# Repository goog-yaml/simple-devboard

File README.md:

# Mk1

Mk1 is the internal name of this project. I am using this as a way to learn about PCB design and embedded systems and make a "final" out of it. The "final" that I have made is a simple, low-cost, ESP32-S3 development board. I originally added tons of sensors and complexity but shaved them off to make the project more attainable. The board functions similar to most other boards, boasting a USB to Serial converter, a sample IMU sensor for SPI testing, and extra essentials like auto reset circuits and a voltage regulator. The board has gone well but I advise most to not use any of these designs for future projects of their own. If you do, don't be surprised when it blows up in your face.

Horizons reviews please check in the /REVIEWERS folder

Journal logs are in the /documentation folder of this repo

The schematic breakdown goes as follows:

# The ESP32-S3

The power rails start with two decoupling capacitors before then merging with reset and boot circuit through pull up resistors

# The IMU

The IMU is a simple MPU-9250 following the schematic posted its online datasheet

# USB to Serial IC

The USB to Serial IC is a FTDI FT231XQ also following the schematic posted in its datasheet

# Auto reset

The auto reset circuit is a set of two 2N3984 transistors that feed into the DTR and RTS pins of the FT231XQ, When a handshake is sent by the flashing device the devboard can enter bootloader states without the need of a button press on the board, though the buttons are still included as a fallback

# USB Port

The port is simple with only two 5K1 resistors for USB power negotiation on both sides.

# Voltage regulator

The voltage regulator includes one TLV75533PDRV from TI and decoupling capacitors on power ins and outs. And the reset pin is tied to power to keep the chip on while the board has power.

# Overall

The PCB is extremely messy.

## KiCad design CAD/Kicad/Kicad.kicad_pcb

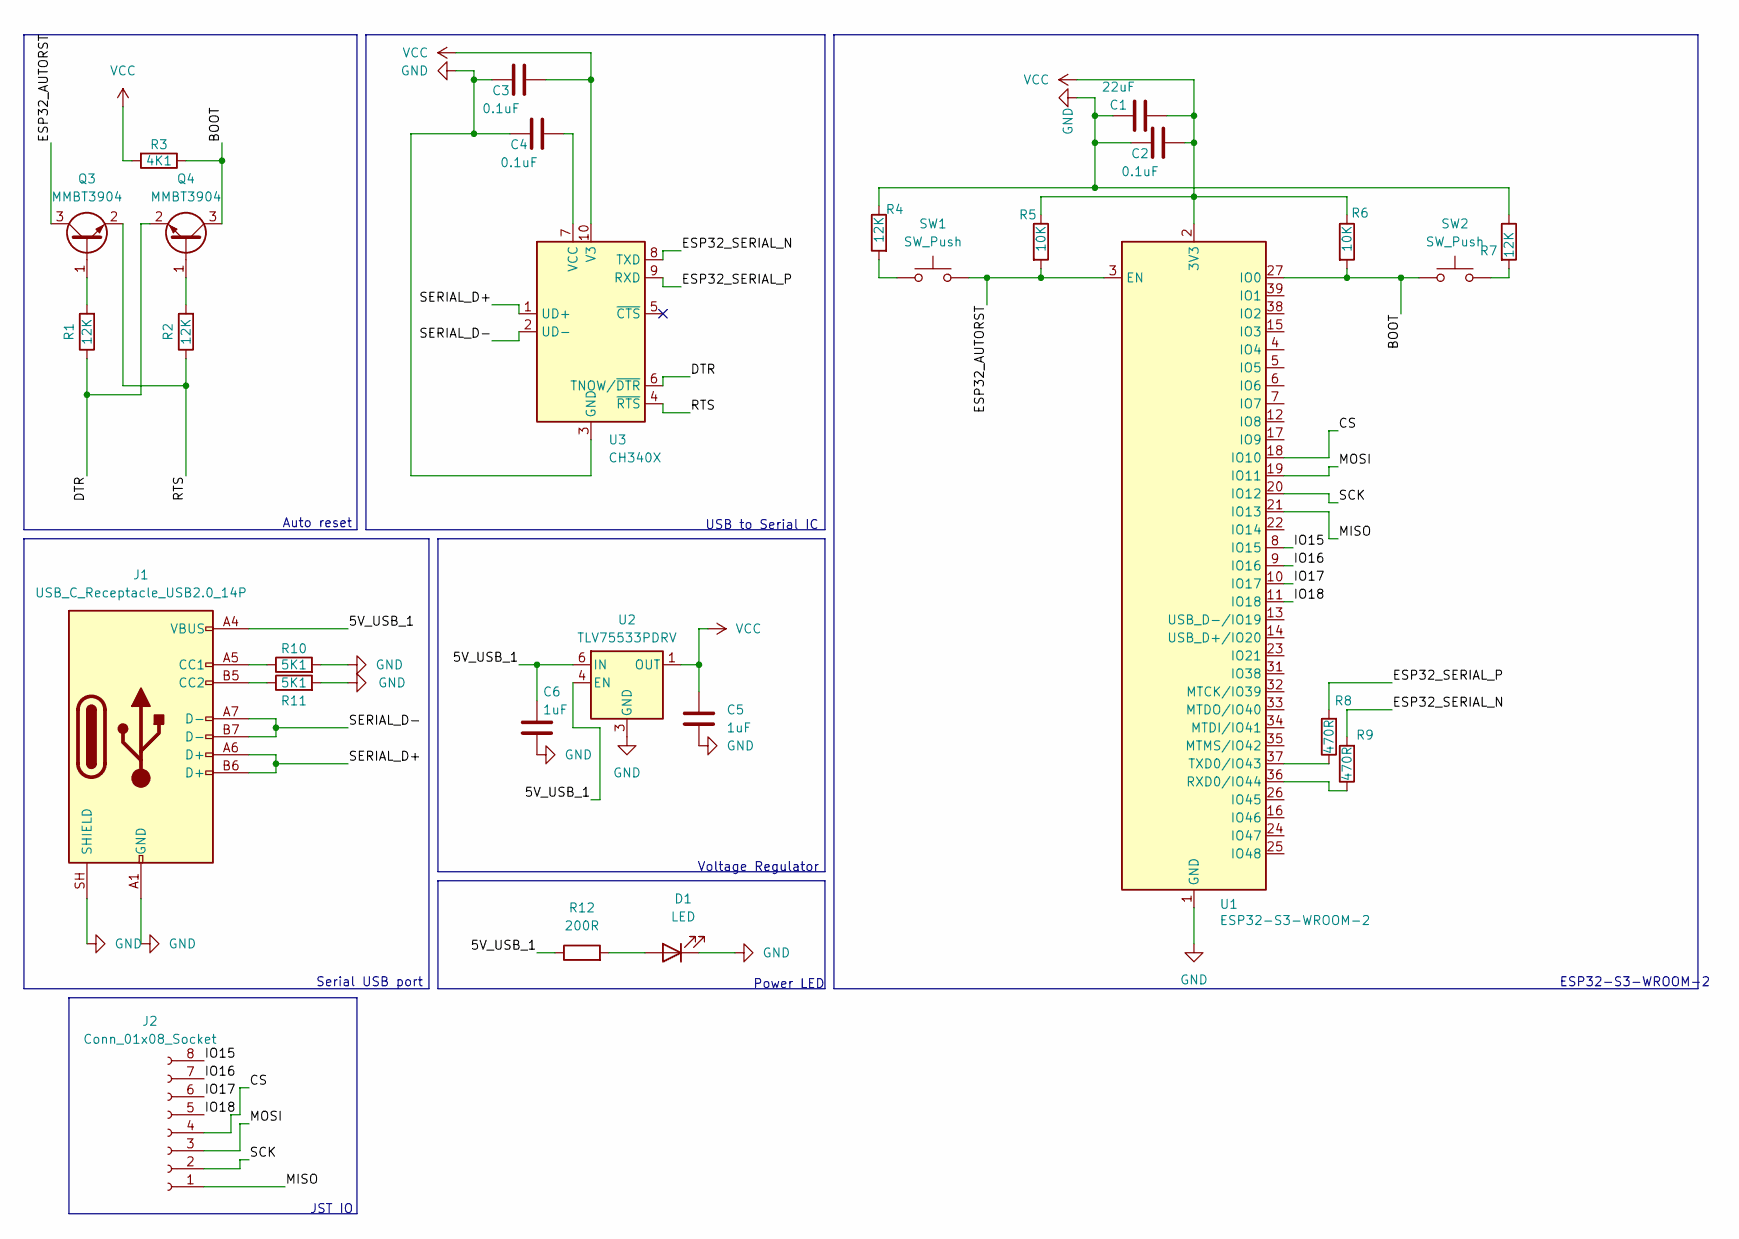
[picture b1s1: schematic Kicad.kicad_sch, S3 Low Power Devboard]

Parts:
C1: 22uF; C_01005_0402Metric; LCSC Part # C105226
C2, C3, C4: 0.1uF; C_01005_0402Metric; LCSC Part # C1525
C5, C6: 1uF; C_01005_0402Metric; LCSC Part # C52923
D1: LED; LED_0201_0603Metric; LCSC Part # C2286
J1: USB_C_Receptacle_USB2.0_14P; USB_C_Receptacle_G-Switch_GT-USB-7025; LCSC Part # C963213
J2: Conn_01x08_Socket; JST_EH_S8B-EH_1x08_P2.50mm_Horizontal; LCSC Part # C265106
Q3, Q4: MMBT3904; SOT-23
R1, R2, R4, R7: 12K; R_0201_0603Metric; LCSC Part # C25752
R3: 4K1; R_0201_0603Metric; LCSC Part # C4109
R5, R6: 10K; R_0201_0603Metric; LCSC Part # C131361
R8, R9: 470R; R_0201_0603Metric; LCSC Part # C177340
R10: 5K1; R_0201_0603Metric; LCSC Part # C25905
R11: 5K1; R_0201_0603Metric; LCSC Part # C177348
R12: 200R; R_01005_0402Metric; LCSC Part # C25087
SW1, SW2: SW_Push; SW_SPST_B3U-1000P; LCSC Part # C231329
U1: ESP32-S3-WROOM-2; LCSC Part # C42417293
U2: TLV75533PDRV; WSON-6-1EP_2x2mm_P0.65mm_EP1x1.6mm; LCSC Part # C2861750
U3: CH340X; MSOP-10_3x3mm_P0.5mm; LCSC Part # C3035748

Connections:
/5V_USB_1: C6.1, J1.A4 (VBUS), J1.A9 (VBUS), J1.B4 (VBUS), J1.B9 (VBUS), R12.1, U2.4 (EN), U2.6 (IN)
/BOOT: Q4.3 (C), R3.1, R6.2, SW2.1, U1.27 (IO0)
/CS: J2.4, U1.18 (IO10)
/DTR: Q4.2 (E), R1.1, U3.6 (TNOW/~DTR)
/ESP32_AUTORST: Q3.3 (C), R5.2, SW1.2, U1.3 (EN)
/ESP32_SERIAL_N: R9.2, U3.8 (TXD)
/ESP32_SERIAL_P: R8.2, U3.9 (RXD)
/IO15: J2.8, U1.8 (IO15)
/IO16: J2.7, U1.9 (IO16)
/IO17: J2.6, U1.10 (IO17)
/IO18: J2.5, U1.11 (IO18)
/MISO: J2.1, U1.21 (IO13)
/MOSI: J2.3, U1.19 (IO11)
/RTS: Q3.2 (E), R2.1, U3.4 (~RTS)
/SCK: J2.2, U1.20 (IO12)
/SERIAL_D+: J1.A6 (D+), J1.B6 (D+), U3.1 (UD+)
/SERIAL_D-: J1.A7 (D-), J1.B7 (D-), U3.2 (UD-)
GND: C1.2, C2.1, C3.1, C4.1, C5.2, C6.2, D1.1 (K), J1.A1 (GND), J1.A12 (GND), J1.B1 (GND), J1.B12 (GND), J1.SH (SHIELD), R4.1, R7.1, R10.2, R11.2, U1.1 (GND), U1.40 (GND), U1.41 (GND), U2.3 (GND), U2.7 (GND), U3.3 (GND)
unnamed: D1.2 (A), R12.2
unnamed: J1.A5 (CC1), R10.1
unnamed: J1.B5 (CC2), R11.1
unnamed: Q3.1 (B), R1.2
unnamed: Q4.1 (B), R2.2
unnamed: R4.2, SW1.1
unnamed: R7.2, SW2.2
unnamed: R9.1, U1.36 (RXD0/IO44)
unnamed: R8.1, U1.37 (TXD0/IO43)
unnamed: C4.2, U3.7 (VCC)
VCC: C1.1, C2.2, C3.2, C5.1, R3.2, R5.1, R6.1, U1.2 (3V3), U2.1 (OUT), U3.10 (V3)

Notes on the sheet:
Power LED
Auto reset
JST IO
Serial USB port
ESP32-S3-WROOM-2
USB to Serial IC
Voltage Regulator

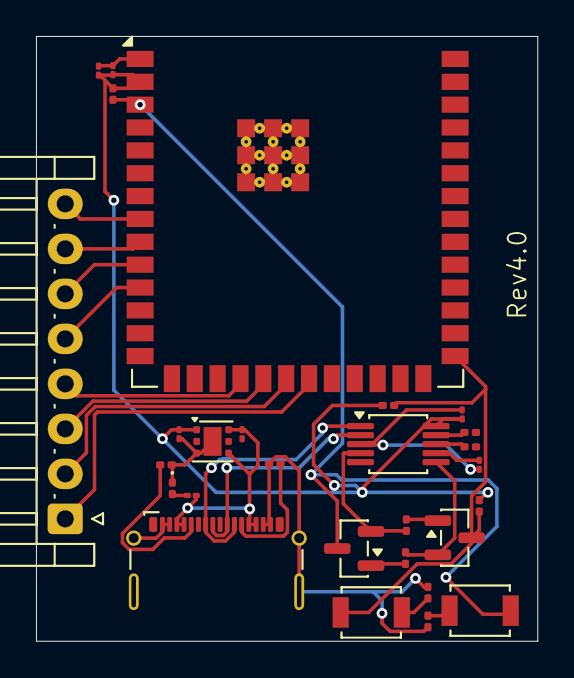
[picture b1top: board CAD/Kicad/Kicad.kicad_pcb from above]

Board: 2 copper layers, 27.8 x 33.6 mm, 28 parts (0 on the bottom side), 29 nets.

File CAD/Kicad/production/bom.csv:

Designator,Footprint,Quantity,Value,LCSC Part #
C1,01005,1,22uF,C105226
"C2, C3, C4",01005,3,0.1uF,C1525
"C5, C6",01005,2,1uF,C52923
D1,0201,1,LED,C2286
J1,USB_C_Receptacle_G-Switch_GT-USB-7025,1,USB_C_Receptacle_USB2.0_14P,C963213
J2,JST_EH_S8B-EH_1x08_P2.50mm_Horizontal,1,Conn_01x08_Socket,C265106
"Q3, Q4",SOT-23,2,MMBT3904,
"R1, R2, R4, R7",0201,4,12K,C25752
R10,0201,1,5K1,C25905
R11,0201,1,5K1,C177348
R12,01005,1,150R,C4109
R3,0201,1,4K1,C4109
"R5, R6",0201,2,10K,C4109
"R8, R9",0201,2,470R,C177340
"SW1, SW2",SW_SPST_B3U-1000P,2,SW_Push,C231329
U1,ESP32-S3-WROOM-2,1,ESP32-S3-WROOM-2,C42417293
U2,WSON-6-1EP_2x2mm_P0.65mm_EP1x1.6mm,1,TLV75533PDRV,C2861750
U3,MSOP-10_3x3mm_P0.5mm,1,CH340X,C3035748

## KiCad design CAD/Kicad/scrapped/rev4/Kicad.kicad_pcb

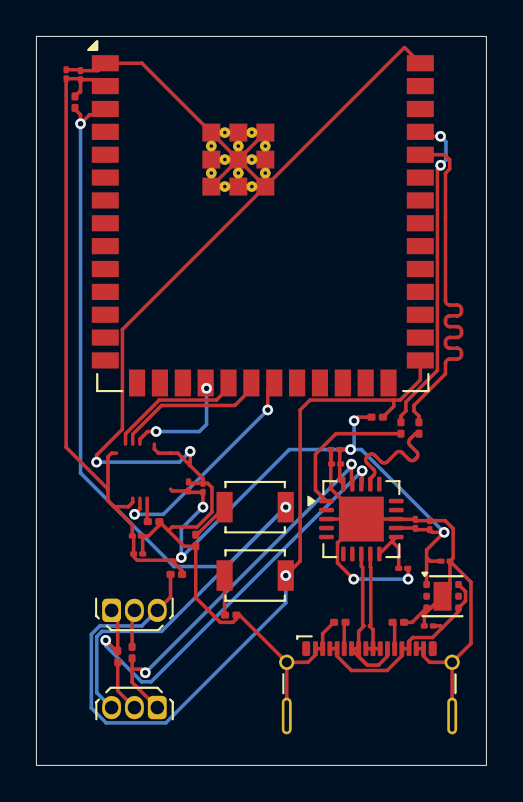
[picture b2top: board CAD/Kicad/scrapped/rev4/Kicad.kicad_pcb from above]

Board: 2 copper layers, 25.0 x 40.5 mm, 33 parts (0 on the bottom side), 19 nets.

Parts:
C3, C4, C9, C10, C14, C20: 0.1uF; C_01005_0402Metric
C5, C6: 1uF; C_01005_0402Metric
C11: 0.1uF; C_0201_0603Metric
C12: 22uF; C_01005_0402Metric
C13, C15, C16, C18: 10uF; C_01005_0402Metric
J1: USB_C_Receptacle_USB2.0_14P; USB_C_Receptacle_G-Switch_GT-USB-7025
Q1, Q2: 2N3904; TO-92Flat
R1, R2: 5K1; R_0201_0603Metric
R3, R9: 10K; R_0201_0603Metric
R4, R5, R6, R8: 12K; R_0201_0603Metric
R7: 4.7K; R_0201_0603Metric
R16, R17: 470R; R_0201_0603Metric
SW1, SW2: SW_Push; SW_SPST_B3U-1000P
U1: ESP32-S3-WROOM-2
U2: TLV75533PDRV; WSON-6-1EP_2x2mm_P0.65mm_EP1x1.6mm
U9: FT231XQ; QFN-20-1EP_4x4mm_P0.5mm_EP2.5x2.5mm

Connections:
/5V_USB_1: C5.1, J1.A4 (VBUS), J1.A9 (VBUS), J1.B4 (VBUS), J1.B9 (VBUS), U2.4 (EN), U2.6 (IN)
/BOOT: Q1.3 (C), R7.1, R9.2, SW2.1, U1.27 (IO0)
/DTR_A: Q1.1 (E), R5.1, U9.18 (~DTR)
/ESP32_AUTORST: Q2.3 (C), R3.2, SW1.2, U1.3 (EN)
/ESP32_SERIAL_N: R17.2, U9.17 (TXD)
/ESP32_SERIAL_P: R16.2, U9.1 (RXD)
/RTS_A: Q2.1 (E), R6.1, U9.19 (~RTS)
/SERIAL_D+: J1.A6 (D+), J1.B6 (D+), U9.8 (USBDP)
/SERIAL_D-: J1.A7 (D-), J1.B7 (D-), U9.9 (USBDM)
/VCC0: C3.2, C4.1, C6.1, C9.1, C10.2, C12.1, C13.1, C14.2, C15.1, C16.1, C18.1, C20.2, R3.1, R7.2, R9.1, U1.2 (3V3), U2.1 (OUT), U9.10 (3V3OUT), U9.11 (~RESET), U9.12 (VCC), U9.20 (VCCIO)
GND: C3.1, C4.2, C5.2, C6.2, C9.2, C10.1, C11.2, C12.2, C13.2, C14.1, C15.2, C16.2, C18.2, C20.1, J1.A1 (GND), J1.A12 (GND), J1.B1 (GND), J1.B12 (GND), J1.SH (SHIELD), R1.2, R2.2, R4.2, R8.1, U1.1 (GND), U1.40 (GND), U1.41 (GND), U2.3 (GND), U2.7 (GND), U9.3 (GND), U9.13 (GND), U9.21 (GND)
unnamed: J1.A5 (CC1), R1.1
unnamed: J1.B5 (CC2), R2.1
unnamed: Q1.2 (B), R6.2
unnamed: Q2.2 (B), R5.2
unnamed: R4.1, SW1.1
unnamed: R8.2, SW2.2
unnamed: R17.1, U1.36 (RXD0/IO44)
unnamed: R16.1, U1.37 (TXD0/IO43)

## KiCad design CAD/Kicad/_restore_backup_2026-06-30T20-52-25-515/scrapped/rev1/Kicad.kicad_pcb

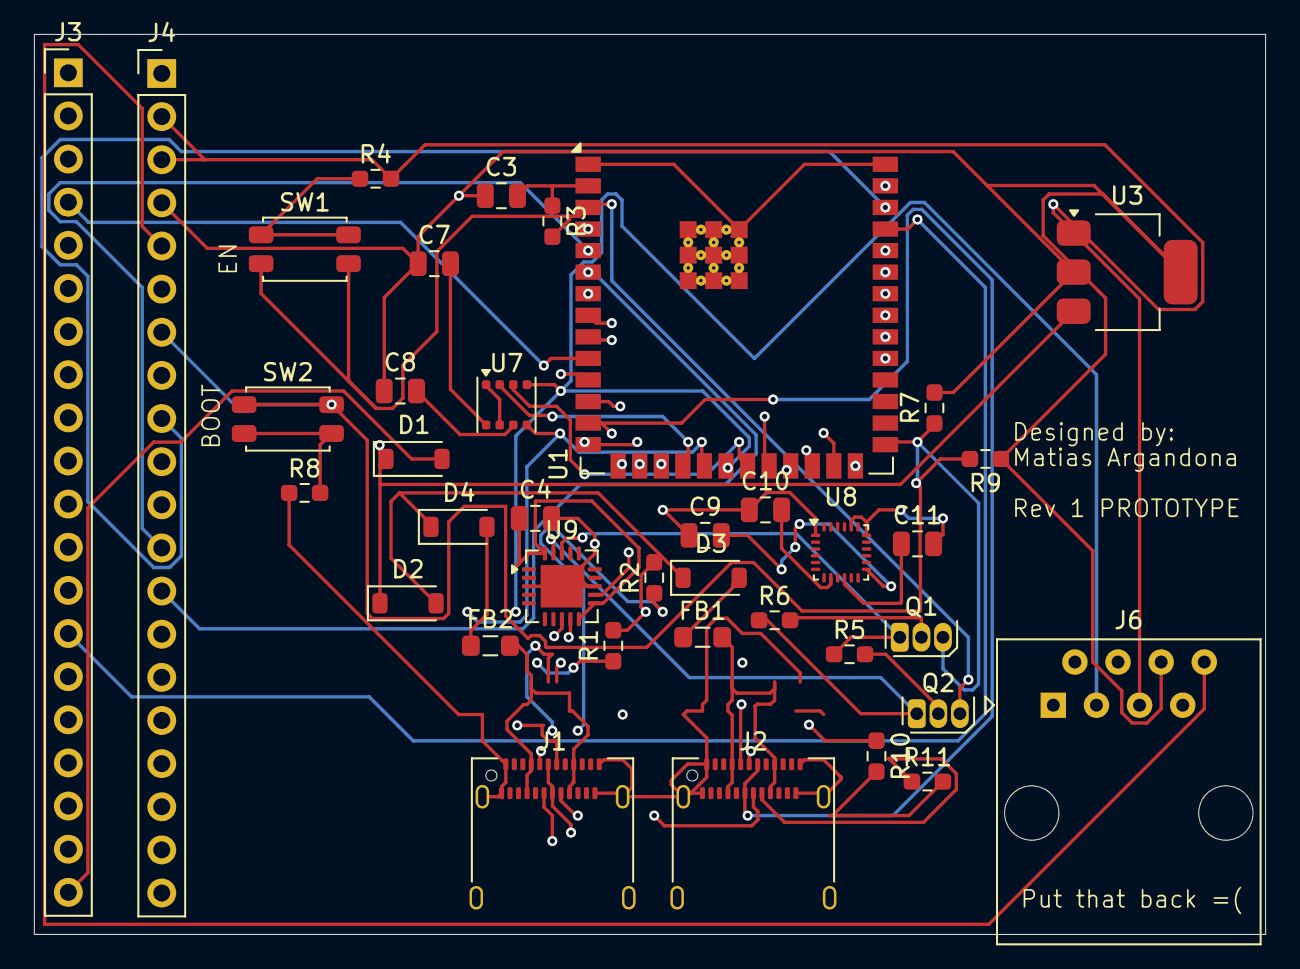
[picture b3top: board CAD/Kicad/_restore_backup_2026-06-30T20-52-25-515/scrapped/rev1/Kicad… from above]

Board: 6 copper layers, 72.5 x 53.0 mm, 38 parts (0 on the bottom side), 61 nets.

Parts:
C3, C4, C7, C8, C9, C10, C11: 0.1uF; C_0805_2012Metric
D1, D2, D3, D4: D_Schottky; D_SOD-123
FB1, FB2: FerriteBead; L_0805_2012Metric_Pad1.05x1.20mm_HandSolder
J1, J2: USB_C_Receptacle_USB2.0_14P; USB_C_Receptacle_Amphenol_12401610E4-2A
J3, J4: Conn_01x20_Pin; PinHeader_1x20_P2.54mm_Vertical
J6: RJ45; RJ45_Amphenol_54602-x08_Horizontal
Q1, Q2: 2N3904; TO-92S
R1, R2, R10, R11: 5K1; R_0603_1608Metric_Pad0.98x0.95mm_HandSolder
R3, R9: 10K; R_0603_1608Metric_Pad0.98x0.95mm_HandSolder
R4, R5, R6, R8: 12K; R_0603_1608Metric_Pad0.98x0.95mm_HandSolder
R7: 4.7K; R_0603_1608Metric_Pad0.98x0.95mm_HandSolder
SW1, SW2: SW_Push; SW_SPST_EVQP2_MiddlePushTravel_H2.5mm
U1: ESP32-S3-WROOM-2
U3: AMS1117-3.3; SOT-223-3_TabPin2
U7: BME680; Bosch_LGA-8_3x3mm_P0.8mm_ClockwisePinNumbering
U8: MPU-9250; InvenSense_QFN-24_3x3mm_P0.4mm
U9: FT231XQ; QFN-20-1EP_4x4mm_P0.5mm_EP2.5x2.5mm

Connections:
/5V_USB_0: D3.2 (A), FB1.1, FB1.2, J2.A4 (VBUS), J2.A9 (VBUS), J2.B4 (VBUS), J2.B9 (VBUS)
/5V_USB_1: D4.2 (A), FB2.1, FB2.2, J1.A4 (VBUS), J1.A9 (VBUS), J1.B4 (VBUS), J1.B9 (VBUS)
/BOOT: J4.7, Q1.3 (C), R7.1, R9.2, SW2.1, U1.27 (IO0)
/CS_BUS_A: J4.17, J6.1, U1.18 (IO10), U7.2 (CSB), U8.22 (~CS)
/DTR_A: Q1.1 (E), R5.1, U9.18 (~DTR)
/ESP32_AUTORST: Q2.3 (C), R3.2, SW1.2, U1.3 (EN)
/ESP32_RXD: J3.15, U1.36 (RXD0/IO44), U9.17 (TXD)
/ESP32_TXD: J3.14, U1.37 (TXD0/IO43), U9.1 (RXD)
/GND: C4.2, C11.2, J1.A1 (GND), J1.A12 (GND), J1.B1 (GND), J1.B12 (GND), J1.SH (SHIELD), J2.A1 (GND), J2.A12 (GND), J2.B1 (GND), J2.B12 (GND), J2.SH (SHIELD), J4.2, J4.3, J6.5, R1.2, R2.2, R4.2, R8.1, R10.2, R11.2, U1.1 (GND), U1.40 (GND), U1.41 (GND), U3.1 (GND), U7.1 (GND), U7.7 (GND), U8.18 (GND), U8.20 (RESV_GND), U9.3 (GND), U9.13 (GND), U9.21 (GND)
/IO1: J4.8, U1.39 (IO1)
/IO2: J4.9, U1.38 (IO2)
/IO3: J4.10, U1.15 (IO3)
/IO4: J4.11, U1.4 (IO4)
/IO5: J4.12, U1.5 (IO5)
/IO6: J4.13, U1.6 (IO6)
/IO7: J4.14, U1.7 (IO7)
/IO8: J4.15, U1.12 (IO8)
/IO9: J4.16, U1.17 (IO9)
/IO14: J3.1, U1.22 (IO14)
/IO15: J3.2, U1.8 (IO15)
/IO16: J3.3, U1.9 (IO16)
/IO17: J3.4, U1.10 (IO17)
/IO18: J3.5, U1.11 (IO18)
/IO21: J3.8, U1.23 (IO21)
/IO38: J3.9, U1.31 (IO38)
/IO39: J3.10, U1.32 (MTCK/IO39)
/IO40: J3.11, U1.33 (MTDO/IO40)
/IO41: J3.12, U1.34 (MTDI/IO41)
/IO42: J3.13, U1.35 (MTMS/IO42)
/IO45: J3.16, U1.26 (IO45)
/IO46: J3.17, U1.16 (IO46)
/IO47: J3.18, U1.24 (IO47)
/IO48: J3.19, U1.25 (IO48)
/IOOUT_A: C4.1, U9.10 (3V3OUT), U9.11 (~RESET), U9.20 (VCCIO)
/MISO_BUS_A: J4.20, J6.2, U1.21 (IO13), U7.3 (SDI), U8.9 (AD0/MISO)
/MOSI_BUS_A: J4.18, J6.4, U1.19 (IO11), U7.5 (SDO), U8.24 (SDA/MOSI)
/NATIVE_D+: J2.A6 (D+), J2.B6 (D+), J3.7, U1.14 (USB_D+/IO20)
/NATIVE_D-: J2.A7 (D-), J2.B7 (D-), J3.6, U1.13 (USB_D-/IO19)
/OROUT: D1.1 (K), D2.1 (K), J4.1, U3.3 (VI)
/RJ43_P7: J4.6, J6.7
/RJ43_P8: J4.5, J6.8
/RTS_A: Q2.1 (E), R6.1, U9.19 (~RTS)
/SCK_BUS_A: J4.19, J6.3, U1.20 (IO12), U7.4 (SCK), U8.23 (SCL/SCLK)
/SERIAL_D+: J1.A6 (D+), J1.B6 (D+), U9.8 (USBDP)
/SERIAL_D-: J1.A7 (D-), J1.B7 (D-), U9.9 (USBDM)
/VCC0: C3.1, C3.2, C7.1, C8.1, C9.1, C10.1, J4.4, J6.6, R3.1, R7.2, R9.1, U1.2 (3V3), U3.2 (VO), U8.1 (RESV_VDDIO), U9.12 (VCC)
/VIN: D1.2 (A), J3.20
unnamed: D2.2 (A), D3.1 (K), D4.1 (K)
unnamed: J1.A5 (CC1), R1.1
unnamed: J1.B5 (CC2), R2.1
unnamed: J2.A5 (CC1), R10.1
unnamed: J2.B5 (CC2), R11.1
unnamed: Q1.2 (B), R6.2
unnamed: Q2.2 (B), R5.2
unnamed: R4.1, SW1.1
unnamed: R8.2, SW2.2
unnamed: C7.2, U7.8 (VDD)
unnamed: C8.2, U7.6 (VDDIO)
unnamed: C11.1, U8.10 (REGOUT)
unnamed: C9.2, U8.13 (VDD)
unnamed: C10.2, U8.8 (VDDIO)

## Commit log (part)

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2026-05-17 Added starting README text
2026-05-19 started KiCAD work on main PCB
2026-05-19 Started KiCAD work
2026-05-19 changed README
2026-05-19 added wakatime project
2026-05-24 Initialize journal with first entry
2026-05-25 More PCB stuff
2026-05-25 Document project updates and new components added
2026-05-25 Added more and finalize basic serial connection
2026-05-25 Pissing Luca off
2026-05-25 dont piss off luca
2026-05-25 more journal entries
2026-05-26 Tweaked out and redid the entire main PCB on a Tuesday Afternoon
2026-05-27 Fixed and added journal entries
2026-05-27 added more journal entries
2026-05-27 more journal tweaks
2026-05-27 It's super late man
2026-05-27 revised sensor board and redid I2C connections to both MCUs
2026-05-27 sensing revisions
2026-05-27 sensing and bus redos and another journal entry
2026-05-27 sensing and bus redos with another journal entry
2026-05-27 Journal entry and small PCB tweaks
2026-05-30 finished schematics and started PCB design
2026-06-02 started PCB
2026-06-03 PCB work and journal entry
2026-06-17 Finalized PCB (Yes!)
2026-06-17 Finished Rev1!
2026-06-19 finished then scrapped rev1
2026-06-19 rando journal tweak
2026-06-21 started rev2
